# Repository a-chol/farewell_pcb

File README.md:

# Farewell

The Farewell is the cheapest 3x3 macropad I could make, with joystick and rotary encoder support.

The cost per unit is around $13 with switches, encoders, diodes and keycaps, for 10 units.

Disclaimer : This is not a final design. Problems identified following the first batch are listed in the "To do" section.

# Features
The PCB provides breakout front and back plate.
It supports : 
 * 9 switches (MX or Alps) in a 3x3 matrix
 * up to two rotary encoders at the top corner positions
 * one dual-axis joystick at the top center position
 * pro-micro footprint for the controller
 * choice of black or printed front and backplate
 * specific frontplate for joystick use

# To do
Here are the problems to be fixed for the second iteration : 
 * Make more space between switch footprints to allow joystick to tilt and keycaps to be mounted (implies non-standard switch spacing)
 * cut PCB corners to make space for standoffs
 * invert pro-micro footprint to have the usb port higher, preventing backplate from blocking cable
 * clean off silk printing from useless markings
 * print the FW on the front-plate in a more visible way (maybe)
 * enlarge a little bit the frontplate joystick cutout
 * move SDA pinhole to prevent confusion in rotary encoder positioning
 * mark back and front of the PCB
 
[Build instructions are available here](BuildInstructions_v1.md)

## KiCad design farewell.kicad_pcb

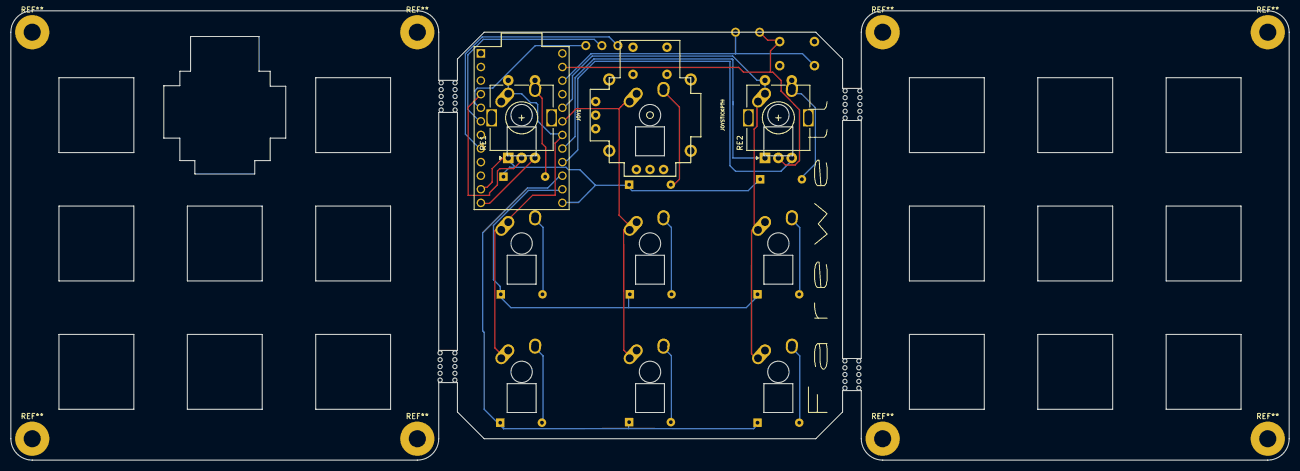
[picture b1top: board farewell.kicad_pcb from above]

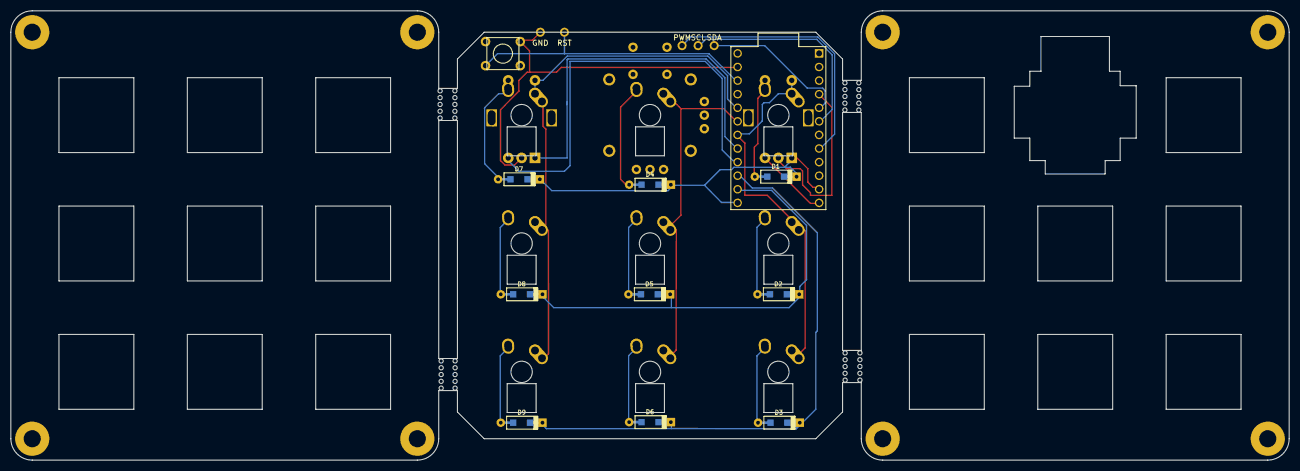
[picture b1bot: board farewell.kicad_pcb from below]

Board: 2 copper layers, 239.0 x 84.0 mm, 28 parts (11 on the bottom side), 25 nets.

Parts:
D1, D2, D3, D4, D5, D6, D7, D8, D9: 1N4148; D_SOD123_axial
EXT1: Conn_01x01; PIN_1
GND_RST1: Conn_01x01; PIN_1
JOY1: JOYSTICKPTH; JOYSTICK
MX1, MX2, MX3, MX4, MX5, MX6, MX7, MX8, MX9: MX-1U; MX-1U-NoLED-NoPCBMount
P?: CONN_1; PIN_1
RE1, RE2: Rotary_Encoder_Switch; RotaryEncoder_Alps_EC11E-Switch_Vertical_H20mm
SCL1: Conn_01x01; PIN_1
SDA1: Conn_01x01; PIN_1
SW1: SW_Push; PushButton_6x6mm_TH_Pretty
U1: 0; ProMicro

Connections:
COL0: MX1.1, MX4.1, MX7.1, RE1.S2, U1.18
COL1: MX2.1, MX5.1, MX8.1, U1.19
COL2: MX3.1, MX6.1, MX9.1, RE2.S2, U1.20
E1A: RE1.A, U1.11
E1B: RE1.B, U1.12
E2A: RE2.A, U1.17
E2B: RE2.B, U1.16
E_G1: RE1.C, U1.4
E_G2: GND_RST1.1, RE2.C, SW1.2, U1.23
JOY_SW_1: D4.2, MX8.2
unnamed: D2.2, MX4.2
unnamed: D3.2, MX1.2
unnamed: D5.2, MX5.2
unnamed: D6.2, MX2.2
unnamed: D8.2, MX6.2
unnamed: D9.2, MX3.2
unnamed: EXT1.1, U1.8
unnamed: SCL1.1, U1.6
unnamed: SDA1.1, U1.5
unnamed: P?.1, SW1.1, U1.22
RE1S1: D1.2, MX7.2, RE1.S1
RE2S1: D7.2, MX9.2, RE2.S1
ROW0: D3.1, D6.1, D9.1, U1.15
ROW1: D2.1, D5.1, D8.1, U1.14
ROW2: D1.1, D4.1, D7.1, U1.13

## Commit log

2019-04-07 farewell with two encoders and middle pro micro
2019-06-13 farewell v1 pcb
2019-06-14 Fixup project path references and add submodules for required libraries
2019-06-19 Add readme and build instructions
2019-06-19 Add farewell picture
2020-02-05 [WIP] Added RGB plate
2020-02-05 V2 fixes + WS2812 holes in pcb
2020-02-26 rgb support with castellated connection
2020-02-27 use female header pins for connecting switch pcb to mcu pcb
2020-05-21 pcb with hybrid sk6812 mini-e/ws2812B footprint and mx/choc compatible switch footprint
2020-09-02 Complete pcb
2020-09-02 rotary encoder space in plates reset to standard size
